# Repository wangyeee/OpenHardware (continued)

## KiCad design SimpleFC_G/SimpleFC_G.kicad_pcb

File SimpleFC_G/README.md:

# SimpleFC_G
The SimpleFCv2 with integrated GPS receiver. Together with its 10 DoF IMU, it has full navigation capability.

***WARNING: The PCB design has not been fabricated, Use with caution!***

## Change List (compare to SimpleFCv2)

- A UBlox ZOE-M8Q GPS receiver is added while external GPS receiver can still be used by changing solder jumpers.
- The onboard DC-DC converter is now MP1470, which supports 2~3s Li-Po.

## Software
SimpleFC was originally designed to run modified version of [AutoQuad](http://autoquad.org/), the source can be found in my [fork](https://github.com/wangyeee/aq_flight_control) of AutoQuad. In additional, port for [PaparazziUAV](http://wiki.paparazziuav.org/wiki/Main_Page) is in progress. It will make SimpleFC support both fixwing and rotorcraft.

## STM32F4 resource usage
The following table summarizes usage of the MCU, details such as pinout and DMA allocation can be found in the [STM32CubeMX](https://www.st.com/en/development-tools/stm32cubemx.html) design file `SimpleFCv2.ioc` in the SimpleFCv2 folder.

| MCU Peripheral | Usage |
|----|----|
| ADC1 | battery monitor and two analog inputs |
| CAN2 | CAN bus |
| I2C1 | [MMC5883MA](https://www.memsic.com/userfiles/files/DataSheets/Magnetic-Sensors-Datasheets/MMC5883MA-RevC.pdf) magnetometer and EEPROM |
| SDIO | TF card slot |
| SPI1 | [ICM20689](http://www.invensense.com/wp-content/uploads/2017/08/ICM-20689-v2.2-002.pdf) gyroscope/accelerometer and [MS5611](https://www.te.com/commerce/DocumentDelivery/DDEController?Action=showdoc&DocId=Data+Sheet%7FMS5611-01BA03%7FB3%7Fpdf%7FEnglish%7FENG_DS_MS5611-01BA03_B3.pdf%7FCAT-BLPS0036) barometer |
| TIM3, TIM4, TIM12 | 8 channel PWM output |
| UART4, USART2 | RC input, support serial, S.Bus or PPM |
| USART1 | telemetry |
| USART3 | GPS receiver |
| USB | DFU or CDC telemetry |

## 3D preview

Front

Back

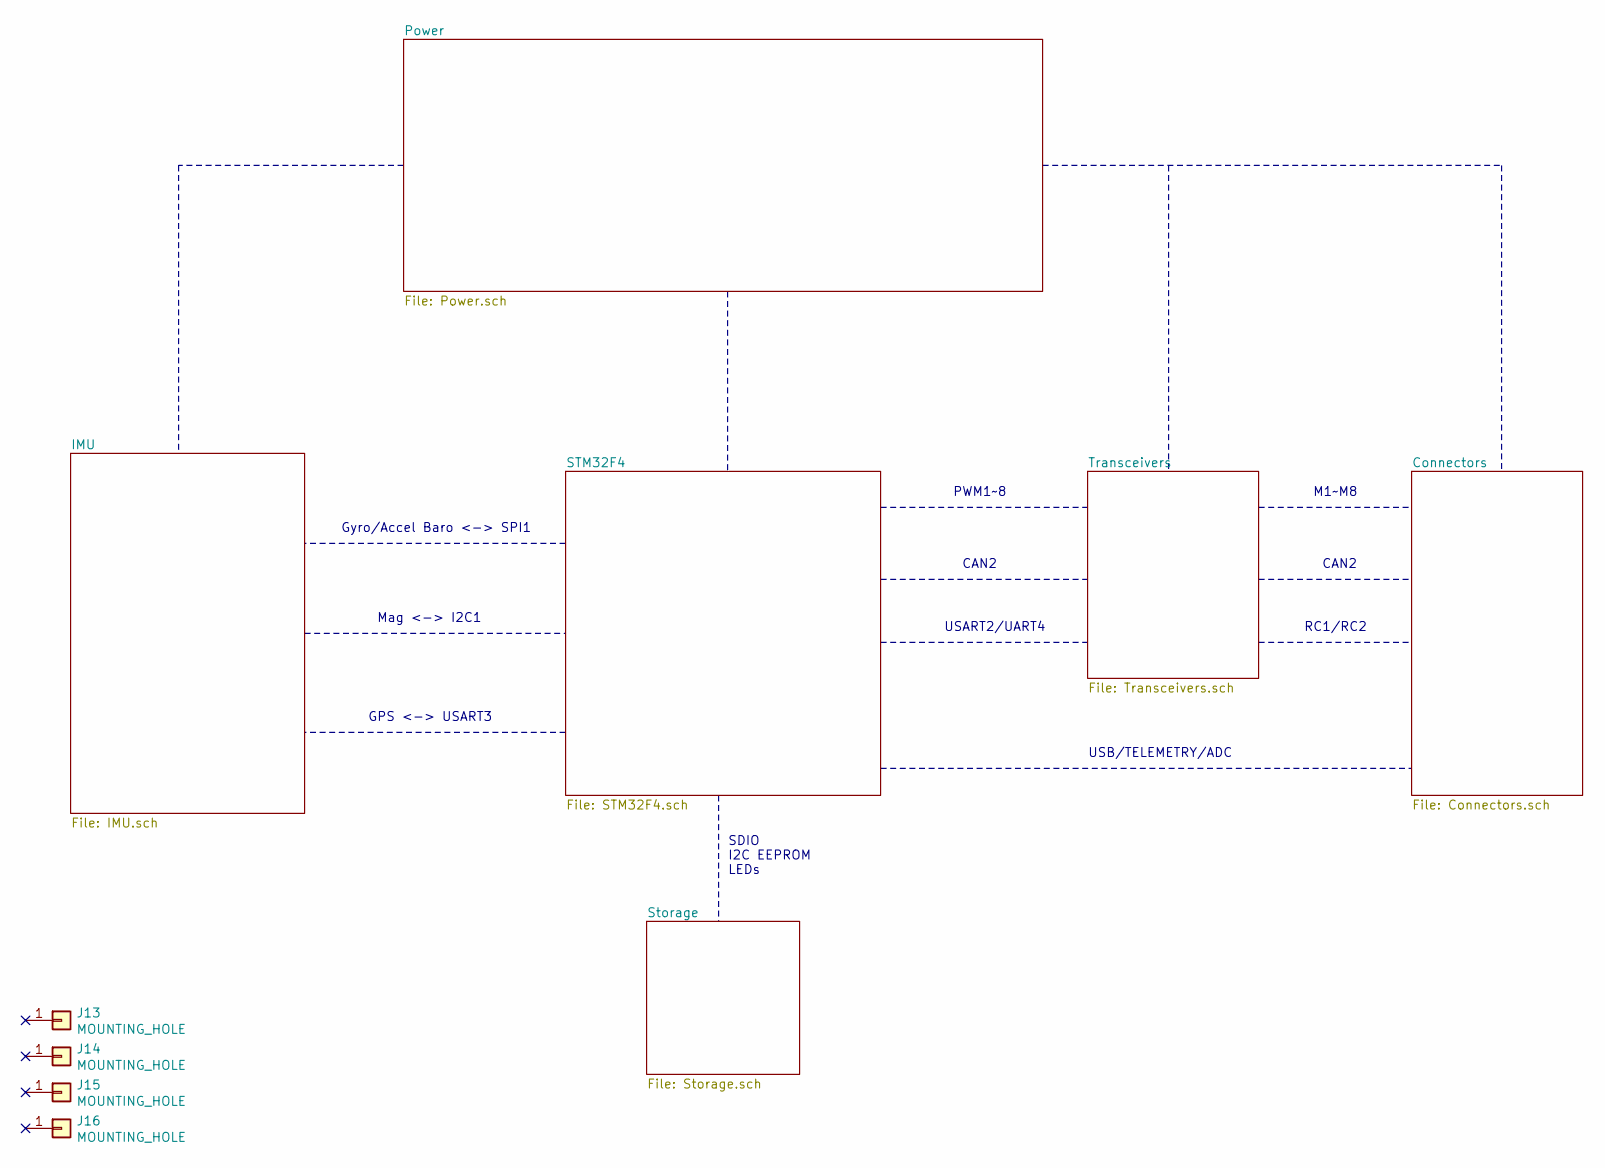
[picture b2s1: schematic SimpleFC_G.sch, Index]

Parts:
J13, J14, J15, J16: MOUNTING_HOLE; MountingHole_3.2mm_M3

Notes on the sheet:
SDIO I2C EEPROM LEDs
Gyro/Accel Baro <-> SPI1
Mag <-> I2C1
GPS <-> USART3
PWM1~~8
CAN2
USART2/UART4
M1~~M8
RC1/RC2
USB/TELEMETRY/ADC

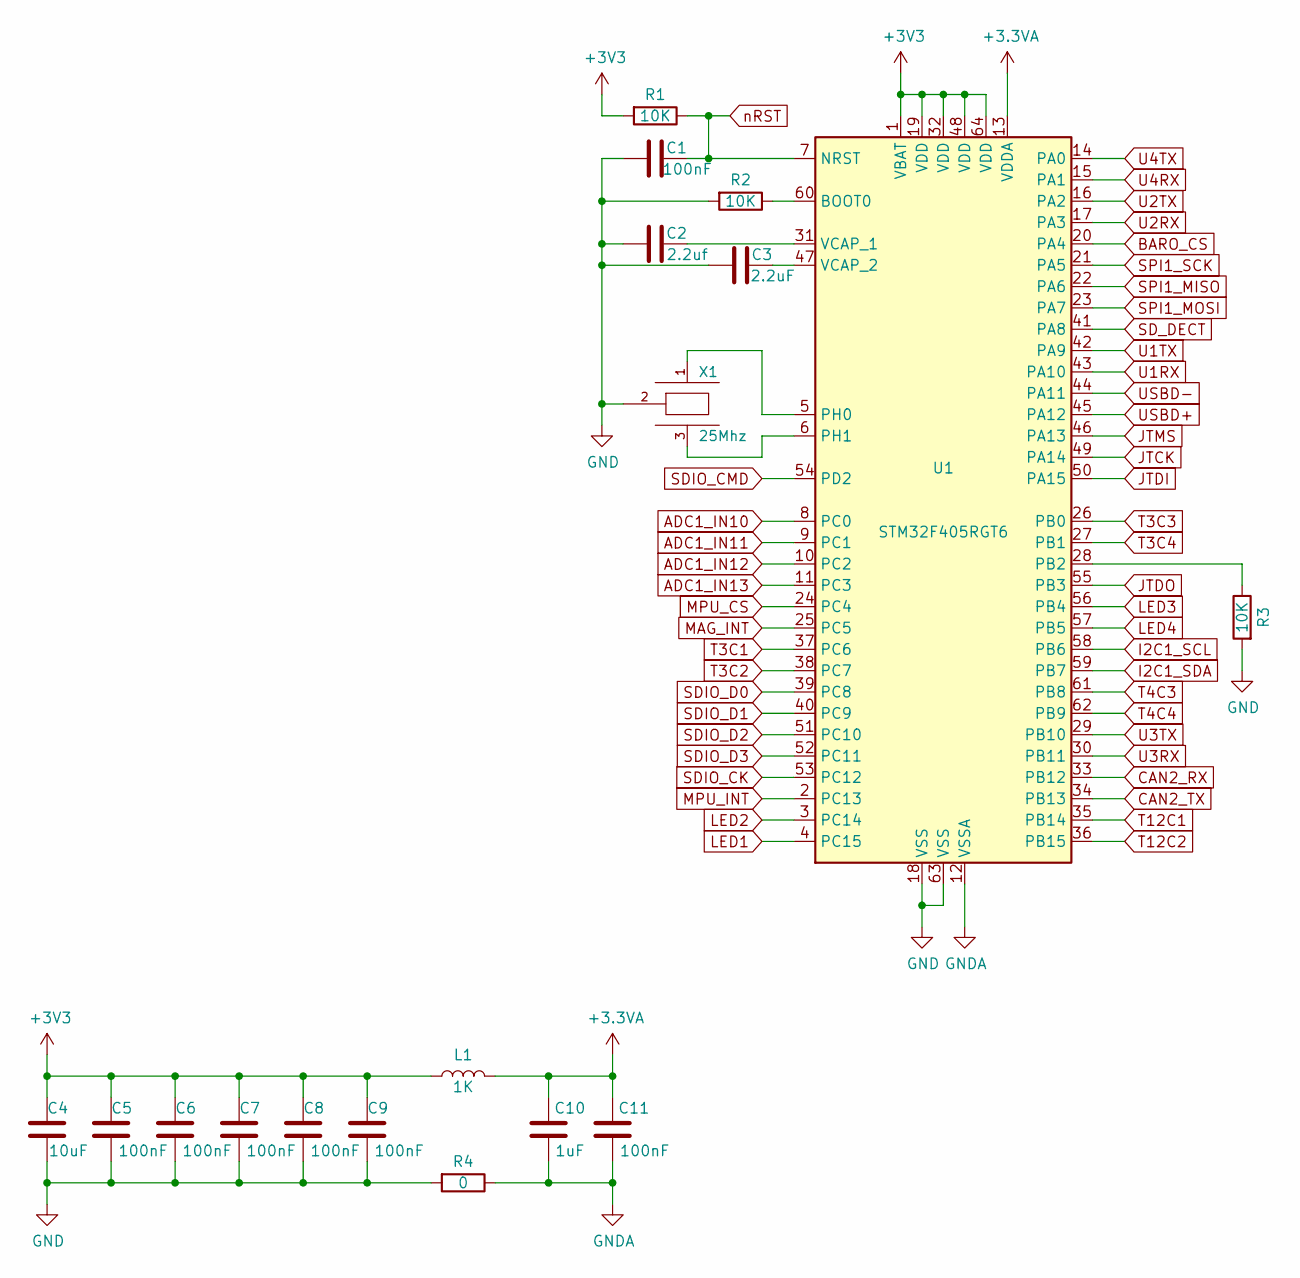
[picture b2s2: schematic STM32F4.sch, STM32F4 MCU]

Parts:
C1, C5, C6, C7, C8, C9, C11: 100nF; C_0603_1608Metric_Pad1.05x0.95mm_HandSolder
C2: 2.2uf; C_0603_1608Metric_Pad1.05x0.95mm_HandSolder
C3: 2.2uF; C_0603_1608Metric_Pad1.05x0.95mm_HandSolder
C4: 10uF; C_0603_1608Metric_Pad1.05x0.95mm_HandSolder
C10: 1uF; C_0603_1608Metric_Pad1.05x0.95mm_HandSolder
L1: 1K; L_0603_1608Metric_Pad1.05x0.95mm_HandSolder
R1, R2, R3: 10K; R_0603_1608Metric_Pad1.05x0.95mm_HandSolder
R4: 0; R_0603_1608Metric_Pad1.05x0.95mm_HandSolder
U1: STM32F405RGT6; LQFP-64_10x10mm_P0.5mm
X1: 25Mhz; CERALOCK-CSTCW

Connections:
+3.3VA: C10.1, C11.1, L1.2, U1.13 (VDDA)
+3V3: C4.1, C5.1, C6.1, C7.1, C8.1, C9.1, L1.1, R1.2, U1.1 (VBAT), U1.19 (VDD), U1.32 (VDD), U1.48 (VDD), U1.64 (VDD); also elsewhere on the board
ADC1_IN10: U1.8 (PC0); also elsewhere on the board
ADC1_IN11: U1.9 (PC1); also elsewhere on the board
ADC1_IN12: U1.10 (PC2); also elsewhere on the board
ADC1_IN13: U1.11 (PC3); also elsewhere on the board
BARO_CS: U1.20 (PA4); also elsewhere on the board
CAN2_RX: U1.33 (PB12); also elsewhere on the board
CAN2_TX: U1.34 (PB13); also elsewhere on the board
GND: C1.2, C2.2, C3.2, C4.2, C5.2, C6.2, C7.2, C8.2, C9.2, R2.2, R3.2, R4.2, U1.18 (VSS), U1.63 (VSS), X1.2; also elsewhere on the board
GNDA: C10.2, C11.2, R4.1, U1.12 (VSSA); also elsewhere on the board
I2C1_SCL: U1.58 (PB6); also elsewhere on the board
I2C1_SDA: U1.59 (PB7); also elsewhere on the board
JTCK: U1.49 (PA14); also elsewhere on the board
JTDI: U1.50 (PA15); also elsewhere on the board
JTDO: U1.55 (PB3); also elsewhere on the board
JTMS: U1.46 (PA13); also elsewhere on the board
LED1: U1.4 (PC15); also elsewhere on the board
LED2: U1.3 (PC14); also elsewhere on the board
LED3: U1.56 (PB4); also elsewhere on the board
LED4: U1.57 (PB5); also elsewhere on the board
MAG_INT: U1.25 (PC5); also elsewhere on the board
MPU_CS: U1.24 (PC4); also elsewhere on the board
MPU_INT: U1.2 (PC13); also elsewhere on the board
unnamed: C2.1, U1.31 (VCAP_1)
unnamed: C3.1, U1.47 (VCAP_2)
unnamed: R2.1, U1.60 (BOOT0)
unnamed: R3.1, U1.28 (PB2)
unnamed: U1.5 (PH0), X1.1
unnamed: U1.6 (PH1), X1.3
SDIO_CK: U1.53 (PC12); also elsewhere on the board
SDIO_CMD: U1.54 (PD2); also elsewhere on the board
SDIO_D0: U1.39 (PC8); also elsewhere on the board
SDIO_D1: U1.40 (PC9); also elsewhere on the board
SDIO_D2: U1.51 (PC10); also elsewhere on the board
SDIO_D3: U1.52 (PC11); also elsewhere on the board
SD_DECT: U1.41 (PA8); also elsewhere on the board
SPI1_MISO: U1.22 (PA6); also elsewhere on the board
SPI1_MOSI: U1.23 (PA7); also elsewhere on the board
SPI1_SCK: U1.21 (PA5); also elsewhere on the board
T3C1: U1.37 (PC6); also elsewhere on the board
T3C2: U1.38 (PC7); also elsewhere on the board
T3C3: U1.26 (PB0); also elsewhere on the board
T3C4: U1.27 (PB1); also elsewhere on the board
T4C3: U1.61 (PB8); also elsewhere on the board
T4C4: U1.62 (PB9); also elsewhere on the board
T12C1: U1.35 (PB14); also elsewhere on the board
T12C2: U1.36 (PB15); also elsewhere on the board
U1RX: U1.43 (PA10); also elsewhere on the board
U1TX: U1.42 (PA9); also elsewhere on the board
U2RX: U1.17 (PA3); also elsewhere on the board
U2TX: U1.16 (PA2); also elsewhere on the board
U3RX: U1.30 (PB11); also elsewhere on the board
U3TX: U1.29 (PB10); also elsewhere on the board
U4RX: U1.15 (PA1); also elsewhere on the board
U4TX: U1.14 (PA0); also elsewhere on the board
USBD+: U1.45 (PA12); also elsewhere on the board
USBD-: U1.44 (PA11); also elsewhere on the board
nRST: C1.1, R1.1, U1.7 (NRST); also elsewhere on the board

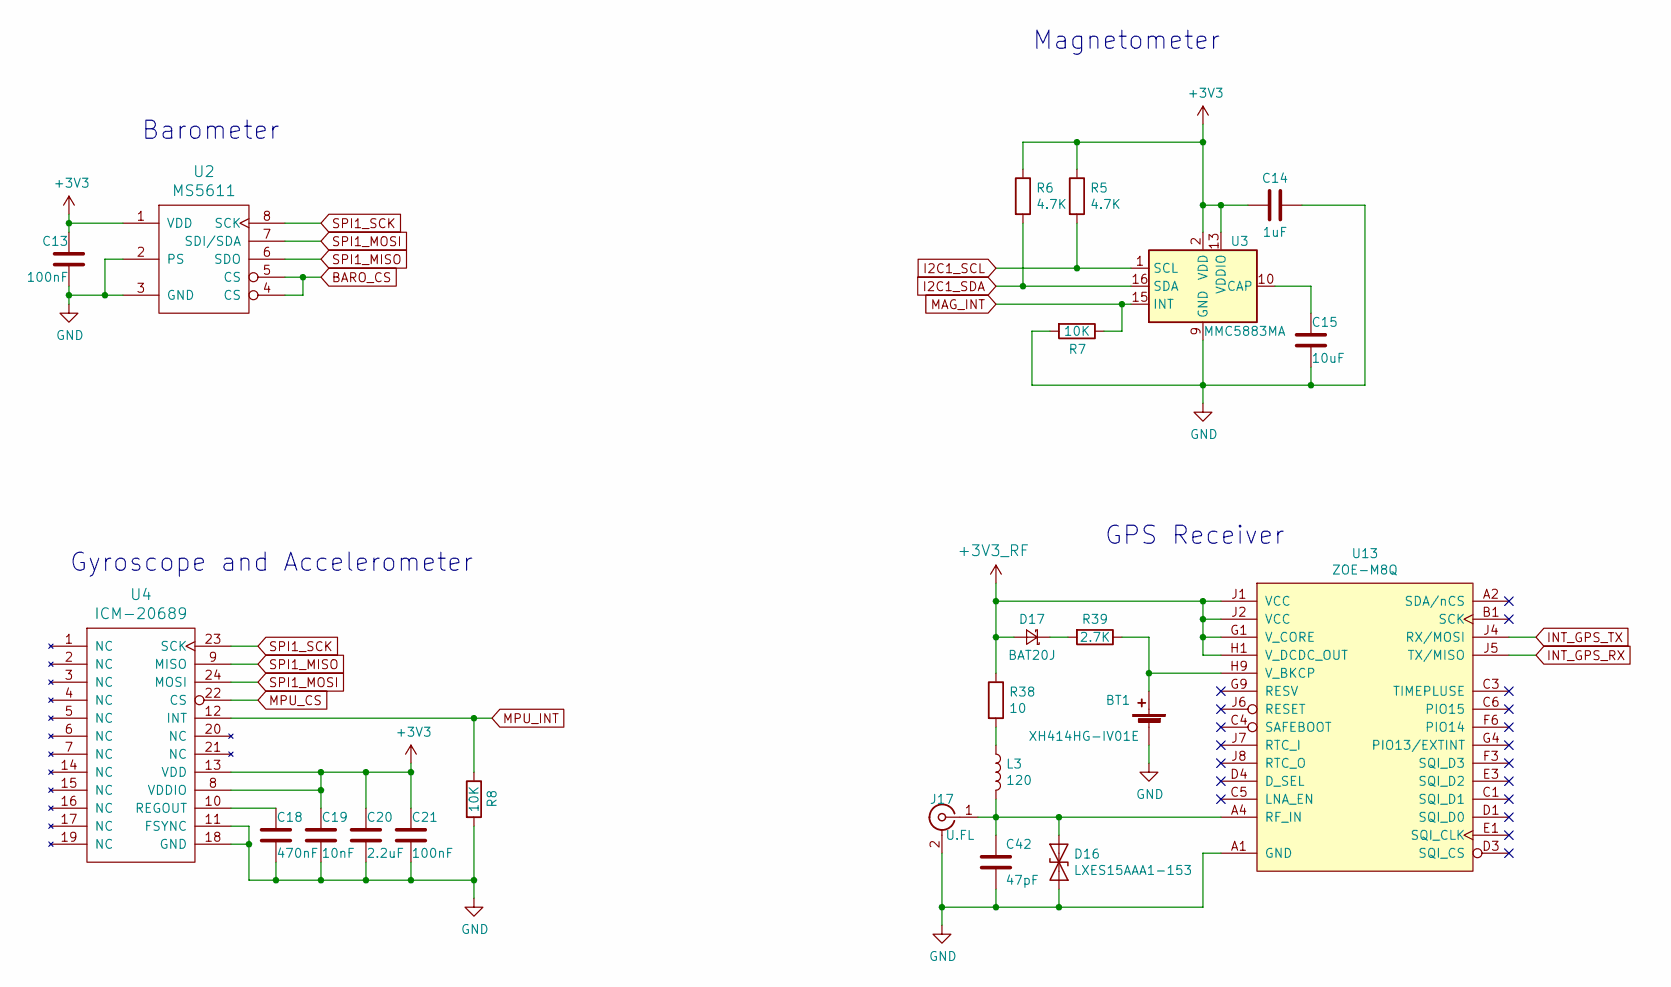
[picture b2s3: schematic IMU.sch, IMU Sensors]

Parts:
BT1: XH414HG-IV01E
C13, C21: 100nF; C_0603_1608Metric_Pad1.05x0.95mm_HandSolder
C14: 1uF; C_0603_1608Metric_Pad1.05x0.95mm_HandSolder
C15: 10uF; C_0603_1608Metric_Pad1.05x0.95mm_HandSolder
C18: 470nF; C_0603_1608Metric_Pad1.05x0.95mm_HandSolder
C19: 10nF; C_0603_1608Metric_Pad1.05x0.95mm_HandSolder
C20: 2.2uF; C_0603_1608Metric_Pad1.05x0.95mm_HandSolder
C42: 47pF; C_0402_1005Metric
D16: LXES15AAA1-153; D_0402_1005Metric
D17: BAT20J; D_SOD-323_HandSoldering
J17: U.FL; U.FL_Molex_MCRF_73412-0110_Vertical
L3: 120; L_0402_1005Metric
R5, R6: 4.7K; R_0603_1608Metric_Pad1.05x0.95mm_HandSolder
R7, R8: 10K; R_0603_1608Metric_Pad1.05x0.95mm_HandSolder
R38: 10; R_0603_1608Metric
R39: 2.7K; R_0603_1608Metric_Pad1.05x0.95mm_HandSolder
U2: MS5611; QFN8-5x3
U3: MMC5883MA; LGA-16_3x3mm_P0.5mm
U4: ICM-20689; QFN-24_MPU
U13: ZOE-M8Q; ZOE-S-LGA51

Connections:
+3V3: C13.1, C14.1, C19.1, C20.1, C21.1, R5.1, R6.1, U2.1 (VDD), U3.2 (VDD), U3.13 (VDDIO), U4.8 (VDDIO), U4.13 (VDD); also elsewhere on the board
+3V3_RF: D17.2 (A), R38.1, U13.G1 (V_CORE), U13.H1 (V_DCDC_OUT), U13.J1 (VCC), U13.J2 (VCC); also elsewhere on the board
BARO_CS: U2.4 (CS), U2.5 (CS); also elsewhere on the board
GND: BT1.2 (-), C13.2, C14.2, C15.2, C18.2, C19.2, C20.2, C21.2, C42.2, D16.2 (A2), J17.2 (Ext), R7.2, R8.2, U2.2 (PS), U2.3 (GND), U3.9 (GND), U3.11 (GND), U4.11 (FSYNC), U4.18 (GND), U13.A1 (GND), U13.A3 (GND), U13.A5 (GND), U13.A7 (GND), U13.A8 (GND), U13.A9 (GND), U13.B9 (GND), U13.C7 (GND), U13.C9 (GND), U13.D6 (GND), U13.D9 (GND), U13.E7 (GND), U13.F7 (GND), U13.G3 (GND), U13.G6 (GND), U13.G7 (GND), U13.J3 (GND), U13.J9 (GND); also elsewhere on the board
I2C1_SCL: R5.2, U3.1 (SCL); also elsewhere on the board
I2C1_SDA: R6.2, U3.16 (SDA); also elsewhere on the board
INT_GPS_RX: U13.J5 (TX/MISO); also elsewhere on the board
INT_GPS_TX: U13.J4 (RX/MOSI); also elsewhere on the board
MAG_INT: R7.1, U3.15 (INT); also elsewhere on the board
MPU_CS: U4.22 (CS); also elsewhere on the board
MPU_INT: R8.1, U4.12 (INT); also elsewhere on the board
unnamed: BT1.1 (+), R39.1, U13.H9 (V_BKCP)
unnamed: C15.1, U3.10 (CAP)
unnamed: C18.1, U4.10 (REGOUT)
unnamed: C42.1, D16.1 (A1), J17.1 (In), L3.2, U13.A4 (RF_IN)
unnamed: D17.1 (K), R39.2
unnamed: L3.1, R38.2
SPI1_MISO: U2.6 (SDO), U4.9 (MISO); also elsewhere on the board
SPI1_MOSI: U2.7 (SDI/SDA), U4.24 (MOSI); also elsewhere on the board
SPI1_SCK: U2.8 (SCK), U4.23 (SCK); also elsewhere on the board

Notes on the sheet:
Barometer
Magnetometer
Gyroscope and Accelerometer
GPS Receiver

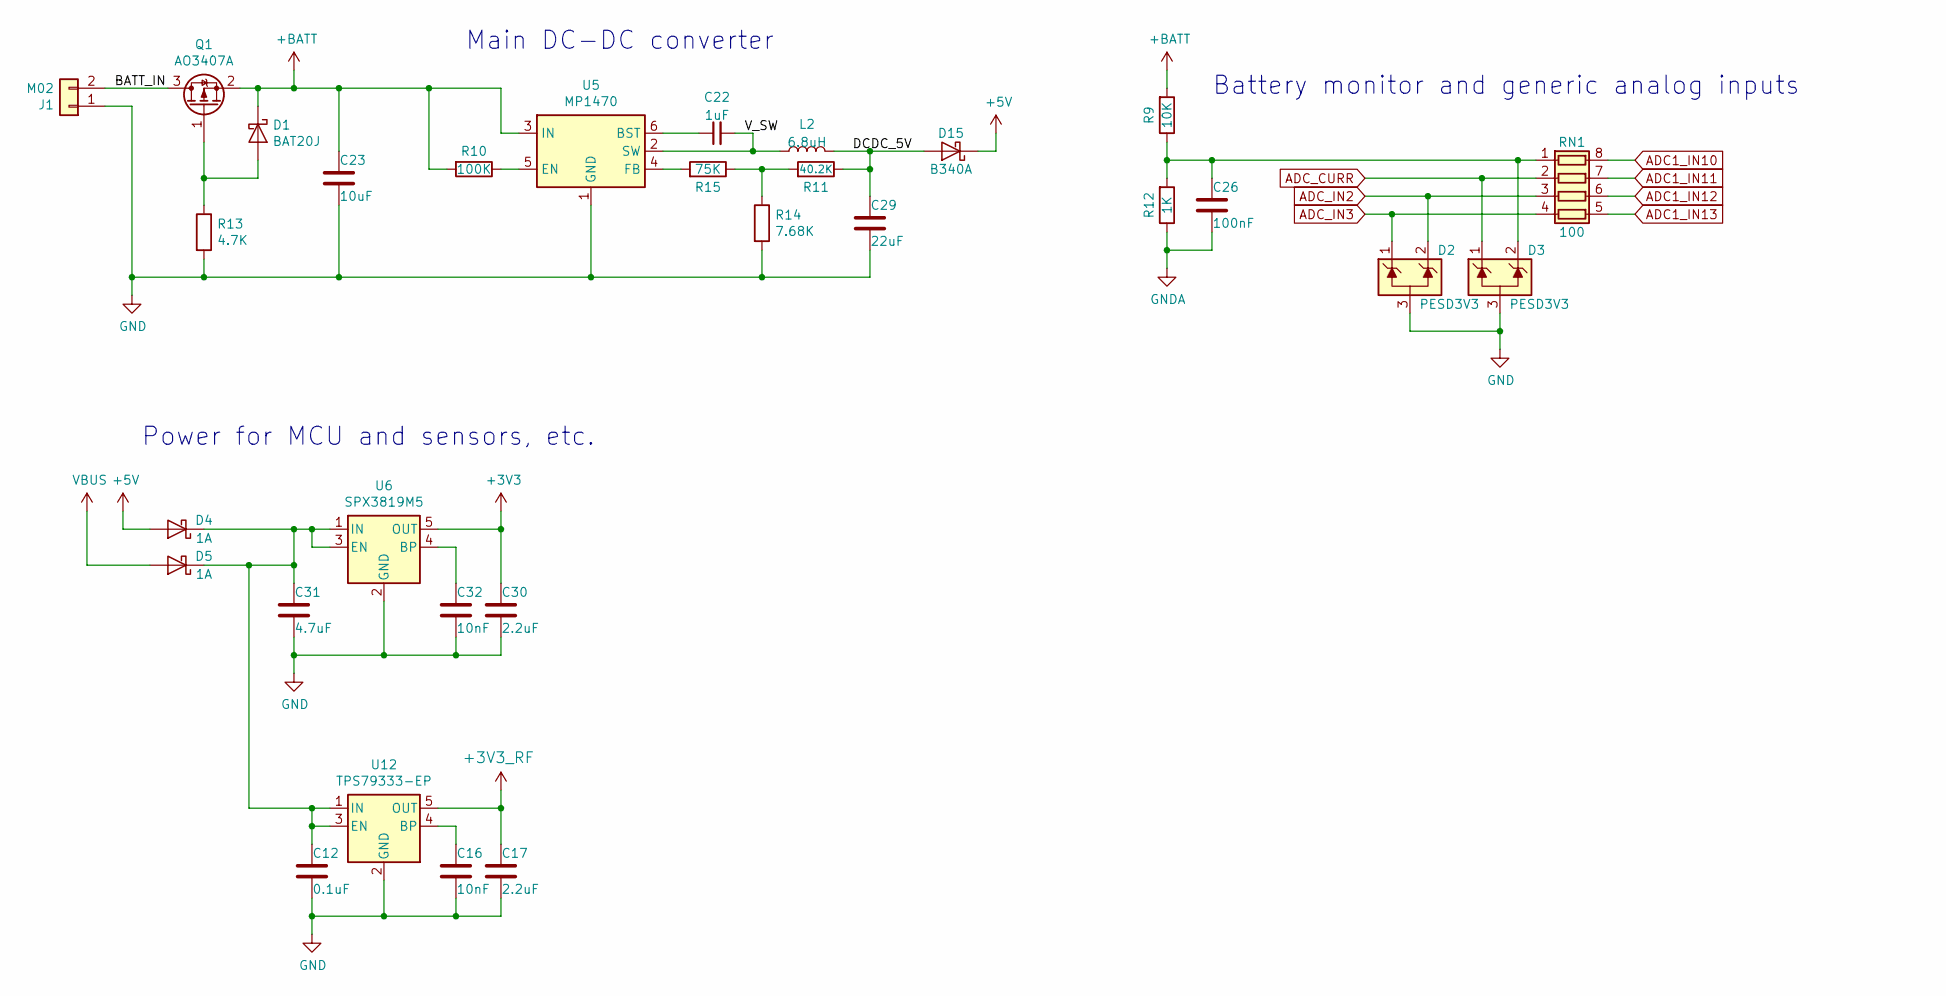
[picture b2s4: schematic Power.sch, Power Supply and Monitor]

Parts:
C12: 0.1uF; C_0603_1608Metric
C16: 10nF; C_0603_1608Metric
C17: 2.2uF; C_0603_1608Metric
C22: 1uF; C_0603_1608Metric_Pad1.05x0.95mm_HandSolder
C23: 10uF; C_1206_3216Metric_Pad1.42x1.75mm_HandSolder
C26: 100nF; C_0603_1608Metric_Pad1.05x0.95mm_HandSolder
C29: 22uF; C_0603_1608Metric_Pad1.05x0.95mm_HandSolder
C30: 2.2uF; C_0603_1608Metric_Pad1.05x0.95mm_HandSolder
C31: 4.7uF; C_0603_1608Metric_Pad1.05x0.95mm_HandSolder
C32: 10nF; C_0603_1608Metric_Pad1.05x0.95mm_HandSolder
D1: BAT20J; D_SOD-323_HandSoldering
D2, D3: PESD3V3; SOT-23
D4, D5: 1A; D_SOD-123
D15: B340A; D_SMA
J1: M02; PinHeader_1x02_P2.54mm_Vertical
L2: 6.8uH; L_Taiyo-Yuden_NR-50xx_HandSoldering
Q1: AO3407A; SOT-23
R9: 10K; R_0603_1608Metric_Pad1.05x0.95mm_HandSolder
R10: 100K; R_0603_1608Metric_Pad1.05x0.95mm_HandSolder
R11: 40.2K; R_0603_1608Metric_Pad1.05x0.95mm_HandSolder
R12: 1K; R_0603_1608Metric_Pad1.05x0.95mm_HandSolder
R13: 4.7K; R_0603_1608Metric_Pad1.05x0.95mm_HandSolder
R14: 7.68K; R_0603_1608Metric_Pad1.05x0.95mm_HandSolder
R15: 75K; R_0603_1608Metric_Pad1.05x0.95mm_HandSolder
RN1: 100; R_Array_Concave_4x0603
U5: MP1470; TSOT-23-6
U6: SPX3819M5; SOT-23-5
U12: TPS79333-EP; SOT-23-5

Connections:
+3V3: C30.1, U6.5 (OUT); also elsewhere on the board
+3V3_RF: C17.1, U12.5 (OUT); also elsewhere on the board
+5V: D4.2 (A), D15.1 (K); also elsewhere on the board
+BATT: C23.1, D1.1 (K), Q1.2 (S), R9.2, R10.2, U5.3 (IN)
/Power/BATT_IN: J1.2, Q1.3 (D)
/Power/DCDC_5V: C29.1, D15.2 (A), L2.2, R11.1
/Power/V_SW: C22.2, L2.1, U5.2 (SW)
ADC1_IN10: RN1.8 (R1.2); also elsewhere on the board
ADC1_IN11: RN1.7 (R2.2); also elsewhere on the board
ADC1_IN12: RN1.6 (R3.2); also elsewhere on the board
ADC1_IN13: RN1.5 (R4.2); also elsewhere on the board
ADC_CURR: D3.1 (K), RN1.2 (R2.1); also elsewhere on the board
ADC_IN2: D2.2 (K), RN1.3 (R3.1); also elsewhere on the board
ADC_IN3: D2.1 (K), RN1.4 (R4.1); also elsewhere on the board
GND: C12.2, C16.2, C17.2, C23.2, C29.2, C30.2, C31.2, C32.2, D2.3 (A), D3.3 (A), J1.1, R13.2, R14.2, U5.1 (GND), U6.2 (GND), U12.2 (GND); also elsewhere on the board
GNDA: C26.2, R12.1; also elsewhere on the board
unnamed: C12.1, C31.1, D4.1 (K), D5.1 (K), U6.1 (IN), U6.3 (EN), U12.1 (IN), U12.3 (EN)
unnamed: C16.1, U12.4 (BP)
unnamed: C22.1, U5.6 (BST)
unnamed: C26.1, D3.2 (K), R9.1, R12.2, RN1.1 (R1.1)
unnamed: C32.1, U6.4 (BP)
unnamed: D1.2 (A), Q1.1 (G), R13.1
unnamed: R10.1, U5.5 (EN)
unnamed: R11.2, R14.1, R15.1
unnamed: R15.2, U5.4 (FB)
VBUS: D5.2 (A); also elsewhere on the board

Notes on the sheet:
Power for MCU and sensors, etc.
Main DC-DC converter
Battery monitor and generic analog inputs

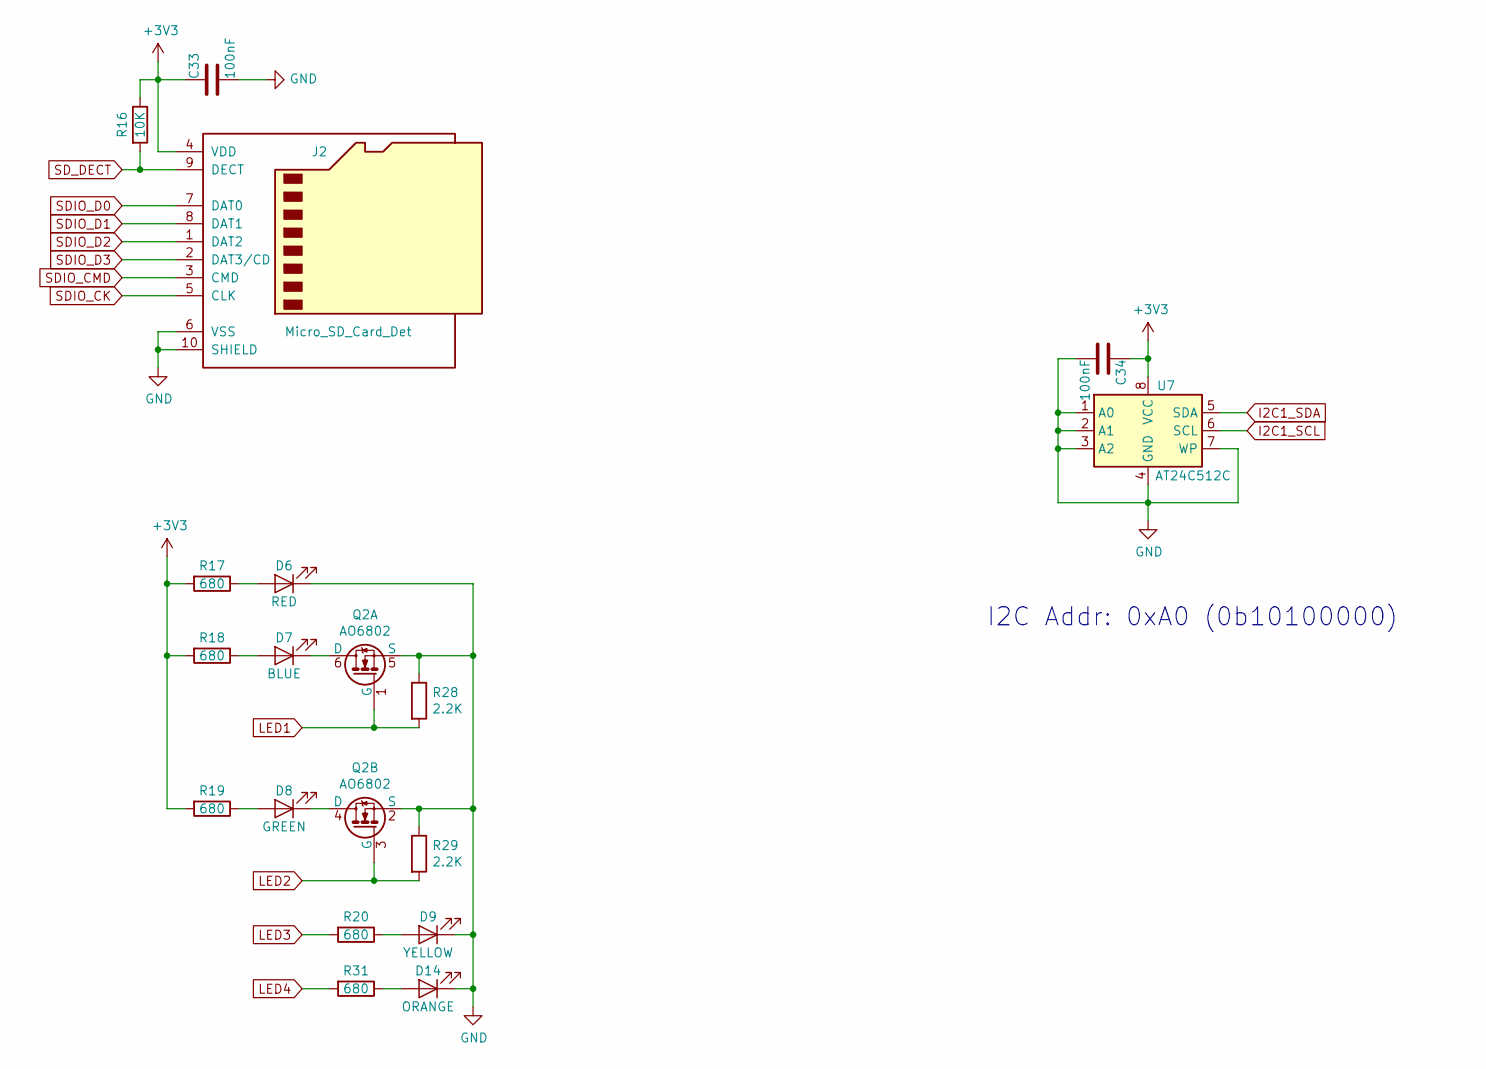
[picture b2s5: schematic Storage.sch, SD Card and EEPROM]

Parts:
C33, C34: 100nF; C_0603_1608Metric_Pad1.05x0.95mm_HandSolder
D6: RED; LED_0603_1608Metric_Pad1.05x0.95mm_HandSolder
D7: BLUE; LED_0603_1608Metric_Pad1.05x0.95mm_HandSolder
D8: GREEN; LED_0603_1608Metric_Pad1.05x0.95mm_HandSolder
D9: YELLOW; LED_0603_1608Metric_Pad1.05x0.95mm_HandSolder
D14: ORANGE; LED_0603_1608Metric_Pad1.05x0.95mm_HandSolder
J2: Micro_SD_Card_Det; TFCARD
Q2: AO6802; SOT-23-6
R16: 10K; R_0603_1608Metric_Pad1.05x0.95mm_HandSolder
R17, R18, R19, R20, R31: 680; R_0603_1608Metric_Pad1.05x0.95mm_HandSolder
R28, R29: 2.2K; R_0603_1608Metric_Pad1.05x0.95mm_HandSolder
U7: AT24C512C; SOIC-8_3.9x4.9mm_P1.27mm

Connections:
+3V3: C33.1, C34.1, J2.4 (VDD), R16.1, R17.2, R18.2, R19.2, U7.8 (VCC); also elsewhere on the board
GND: C33.2, C34.2, D6.1 (K), D9.1 (K), D14.1 (K), J2.6 (VSS), J2.10 (SHIELD), Q2.2 (S), Q2.5 (S), R28.1, R29.1, U7.1 (A0), U7.2 (A1), U7.3 (A2), U7.4 (GND), U7.7 (WP); also elsewhere on the board
I2C1_SCL: U7.6 (SCL); also elsewhere on the board
I2C1_SDA: U7.5 (SDA); also elsewhere on the board
LED1: Q2.1 (G), R28.2; also elsewhere on the board
LED2: Q2.3 (G), R29.2; also elsewhere on the board
LED3: R20.2; also elsewhere on the board
LED4: R31.2; also elsewhere on the board
unnamed: D6.2 (A), R17.1
unnamed: D7.1 (K), Q2.6 (D)
unnamed: D7.2 (A), R18.1
unnamed: D8.1 (K), Q2.4 (D)
unnamed: D8.2 (A), R19.1
unnamed: D9.2 (A), R20.1
unnamed: D14.2 (A), R31.1
SDIO_CK: J2.5 (CLK); also elsewhere on the board
SDIO_CMD: J2.3 (CMD); also elsewhere on the board
SDIO_D0: J2.7 (DAT0); also elsewhere on the board
SDIO_D1: J2.8 (DAT1); also elsewhere on the board
SDIO_D2: J2.1 (DAT2); also elsewhere on the board
SDIO_D3: J2.2 (DAT3/CD); also elsewhere on the board
SD_DECT: J2.9 (DECT), R16.2; also elsewhere on the board

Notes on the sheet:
I2C Addr: 0xA0 (0b10100000)

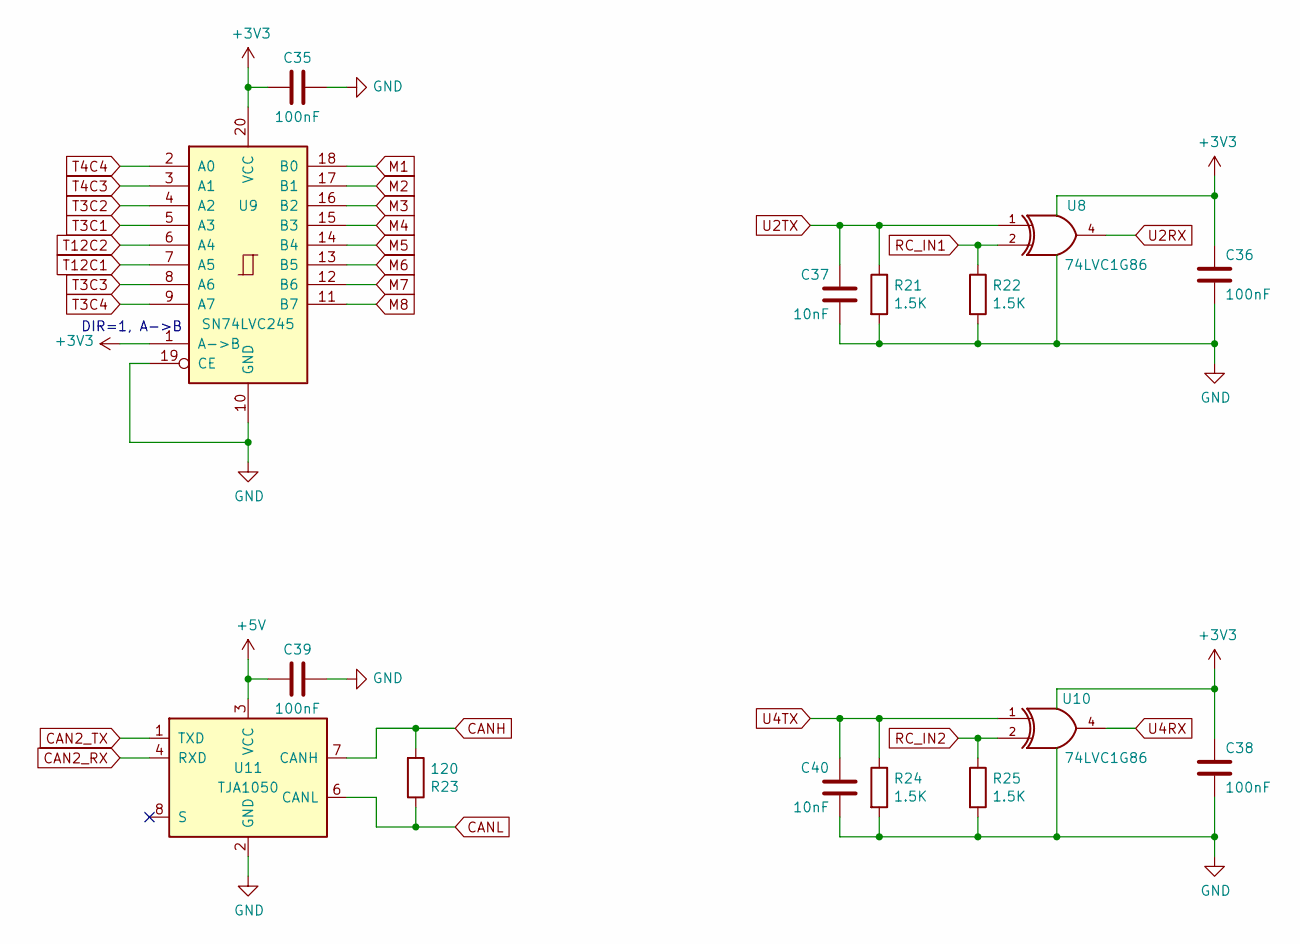
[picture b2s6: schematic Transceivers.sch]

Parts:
C35, C36, C38, C39: 100nF; C_0603_1608Metric_Pad1.05x0.95mm_HandSolder
C37, C40: 10nF; C_0603_1608Metric_Pad1.05x0.95mm_HandSolder
R21, R22, R24, R25: 1.5K; R_0603_1608Metric_Pad1.05x0.95mm_HandSolder
R23: 120; R_0603_1608Metric_Pad1.05x0.95mm_HandSolder
U8, U10: 74LVC1G86; SOT-23-5
U9: SN74LVC245; TSSOP-20_4.4x6.5mm_P0.65mm
U11: TJA1050; SOIC-8_3.9x4.9mm_P1.27mm

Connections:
+3V3: C35.1, C36.1, C38.1, U8.5 (VCC), U9.1 (A->B), U9.20 (VCC), U10.5 (VCC); also elsewhere on the board
+5V: C39.1, U11.3 (VCC); also elsewhere on the board
CAN2_RX: U11.4 (RXD); also elsewhere on the board
CAN2_TX: U11.1 (TXD); also elsewhere on the board
CANH: R23.2, U11.7 (CANH); also elsewhere on the board
CANL: R23.1, U11.6 (CANL); also elsewhere on the board
GND: C35.2, C36.2, C37.2, C38.2, C39.2, C40.2, R21.2, R22.2, R24.2, R25.2, U8.3 (GND), U9.10 (GND), U9.19 (CE), U10.3 (GND), U11.2 (GND); also elsewhere on the board
M1: U9.18 (B0); also elsewhere on the board
M2: U9.17 (B1); also elsewhere on the board
M3: U9.16 (B2); also elsewhere on the board
M4: U9.15 (B3); also elsewhere on the board
M5: U9.14 (B4); also elsewhere on the board
M6: U9.13 (B5); also elsewhere on the board
M7: U9.12 (B6); also elsewhere on the board
M8: U9.11 (B7); also elsewhere on the board
RC_IN1: R22.1, U8.2; also elsewhere on the board
RC_IN2: R25.1, U10.2; also elsewhere on the board
T3C1: U9.5 (A3); also elsewhere on the board
T3C2: U9.4 (A2); also elsewhere on the board
T3C3: U9.8 (A6); also elsewhere on the board
T3C4: U9.9 (A7); also elsewhere on the board
T4C3: U9.3 (A1); also elsewhere on the board
T4C4: U9.2 (A0); also elsewhere on the board
T12C1: U9.7 (A5); also elsewhere on the board
T12C2: U9.6 (A4); also elsewhere on the board
U2RX: U8.4; also elsewhere on the board
U2TX: C37.1, R21.1, U8.1; also elsewhere on the board
U4RX: U10.4; also elsewhere on the board
U4TX: C40.1, R24.1, U10.1; also elsewhere on the board

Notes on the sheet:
DIR=1, A->B

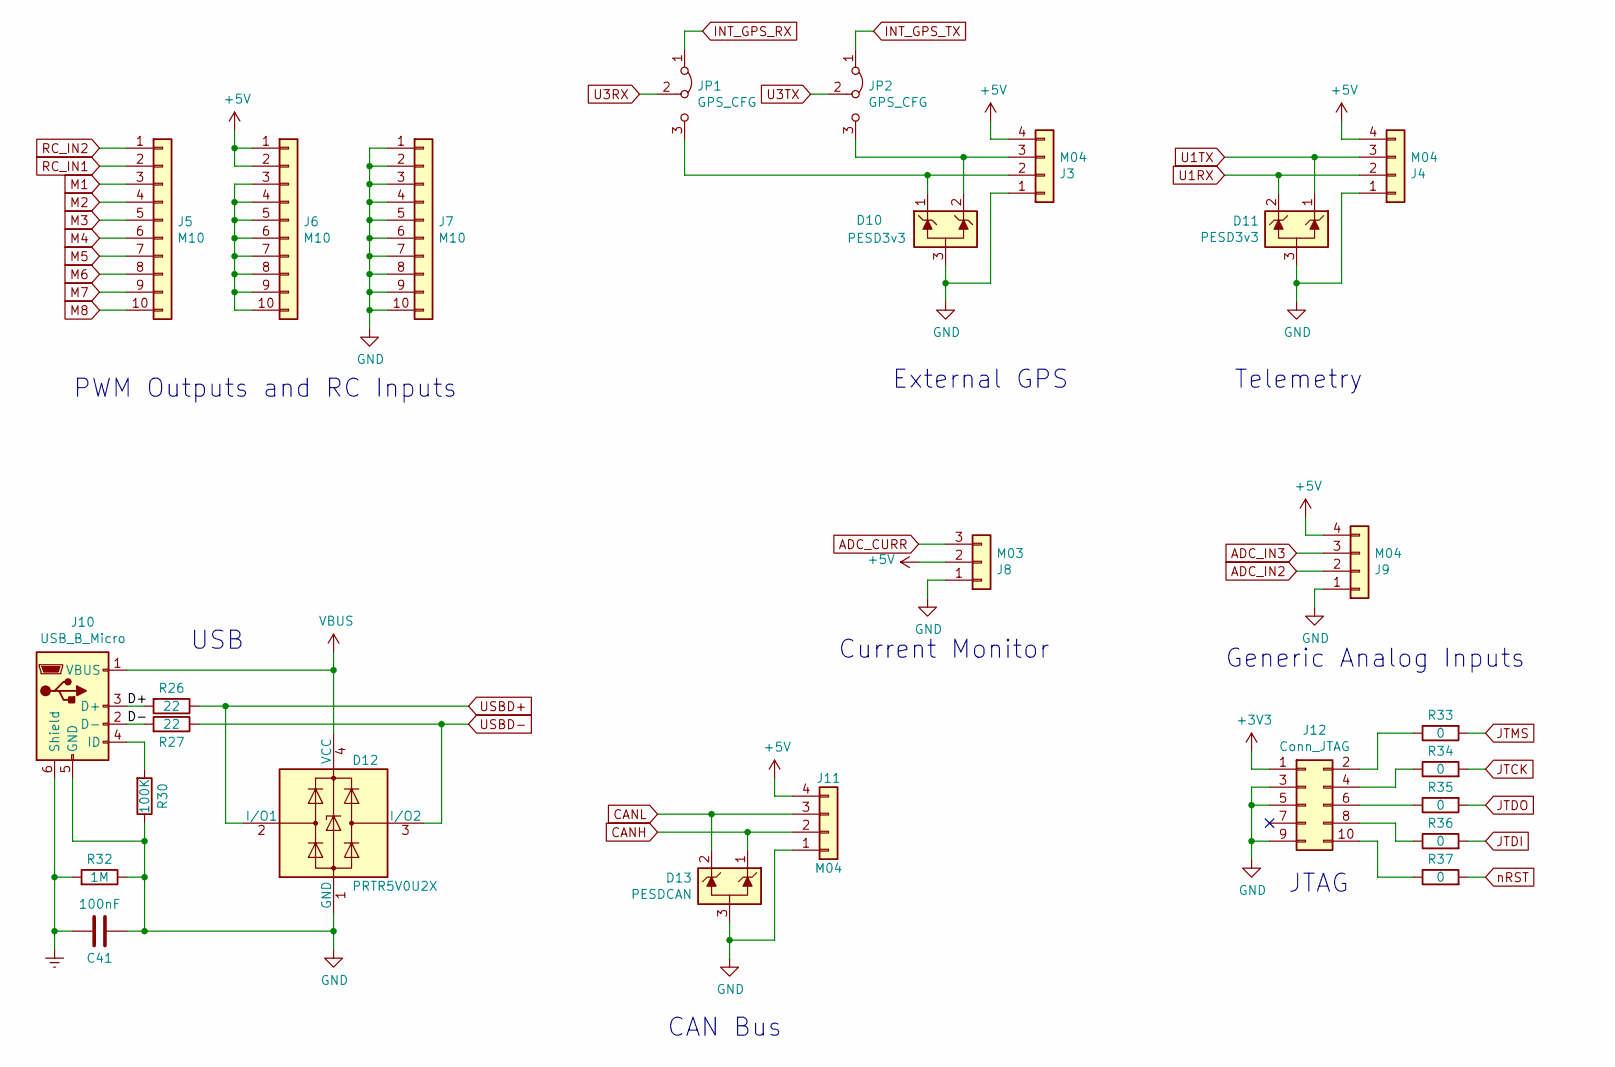
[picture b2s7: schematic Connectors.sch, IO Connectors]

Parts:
C41: 100nF; C_0603_1608Metric_Pad1.05x0.95mm_HandSolder
D10, D11: PESD3v3; SOT-23
D12: PRTR5V0U2X; SOT143B
D13: PESDCAN; SOT-23
J3, J4, J9, J11: M04; PinHeader_1x04_P2.54mm_Vertical
J5, J6, J7: M10; PinHeader_1x10_P2.54mm_Vertical
J8: M03; PinHeader_1x03_P2.54mm_Vertical
J10: USB_B_Micro; USB-AB-MICRO
J12: Conn_JTAG; PinHeader_2x05_P1.27mm_Vertical_SMD
JP1, JP2: GPS_CFG; JUMPER_0402
R26, R27: 22; R_0603_1608Metric_Pad1.05x0.95mm_HandSolder
R30: 100K; R_0603_1608Metric_Pad1.05x0.95mm_HandSolder
R32: 1M; R_0603_1608Metric_Pad1.05x0.95mm_HandSolder
R33, R34, R35, R36, R37: 0; R_0402_1005Metric

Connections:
+3V3: J12.1; also elsewhere on the board
+5V: J3.4, J4.4, J6.1, J6.2, J8.2, J9.4, J11.4; also elsewhere on the board
/Connectors/D+: J10.3 (D+), R26.2
/Connectors/D-: J10.2 (D-), R27.2
ADC_CURR: J8.3; also elsewhere on the board
ADC_IN2: J9.2; also elsewhere on the board
ADC_IN3: J9.3; also elsewhere on the board
CANH: D13.1 (K), J11.2; also elsewhere on the board
CANL: D13.2 (K), J11.3; also elsewhere on the board
Earth: C41.1, J10.6 (Shield), R32.2
GND: C41.2, D10.3 (A), D11.3 (A), D12.1 (GND), D13.3 (A), J3.1, J4.1, J7.1, J7.2, J7.3, J7.4, J7.5, J7.6, J7.7, J7.8, J7.9, J7.10, J8.1, J9.1, J10.5 (GND), J11.1, J12.3, J12.5, J12.9, R30.1, R32.1; also elsewhere on the board
INT_GPS_RX: JP1.1 (A); also elsewhere on the board
INT_GPS_TX: JP2.1 (A); also elsewhere on the board
JTCK: R34.2; also elsewhere on the board
JTDI: R36.2; also elsewhere on the board
JTDO: R35.2; also elsewhere on the board
JTMS: R33.2; also elsewhere on the board
M1: J5.3; also elsewhere on the board
M2: J5.4; also elsewhere on the board
M3: J5.5; also elsewhere on the board
M4: J5.6; also elsewhere on the board
M5: J5.7; also elsewhere on the board
M6: J5.8; also elsewhere on the board
M7: J5.9; also elsewhere on the board
M8: J5.10; also elsewhere on the board
unnamed: D10.1 (K), J3.2, JP1.3 (B)
unnamed: D10.2 (K), J3.3, JP2.3 (B)
unnamed: J6.3, J6.4, J6.5, J6.6, J6.7, J6.8, J6.9, J6.10
unnamed: J10.4 (ID), R30.2
unnamed: J12.2, R33.1
unnamed: J12.4, R34.1
unnamed: J12.6, R35.1
unnamed: J12.8, R36.1
unnamed: J12.10, R37.1
RC_IN1: J5.2; also elsewhere on the board
RC_IN2: J5.1; also elsewhere on the board
U1RX: D11.2 (K), J4.2; also elsewhere on the board
U1TX: D11.1 (K), J4.3; also elsewhere on the board
U3RX: JP1.2 (C); also elsewhere on the board
U3TX: JP2.2 (C); also elsewhere on the board
USBD+: D12.2 (I/O1), R26.1; also elsewhere on the board
USBD-: D12.3 (I/O2), R27.1; also elsewhere on the board
VBUS: D12.4 (VCC), J10.1 (VBUS); also elsewhere on the board
nRST: R37.2; also elsewhere on the board

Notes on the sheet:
USB
PWM Outputs and RC Inputs
CAN Bus
Telemetry
Current Monitor
Generic Analog Inputs
JTAG
External GPS
